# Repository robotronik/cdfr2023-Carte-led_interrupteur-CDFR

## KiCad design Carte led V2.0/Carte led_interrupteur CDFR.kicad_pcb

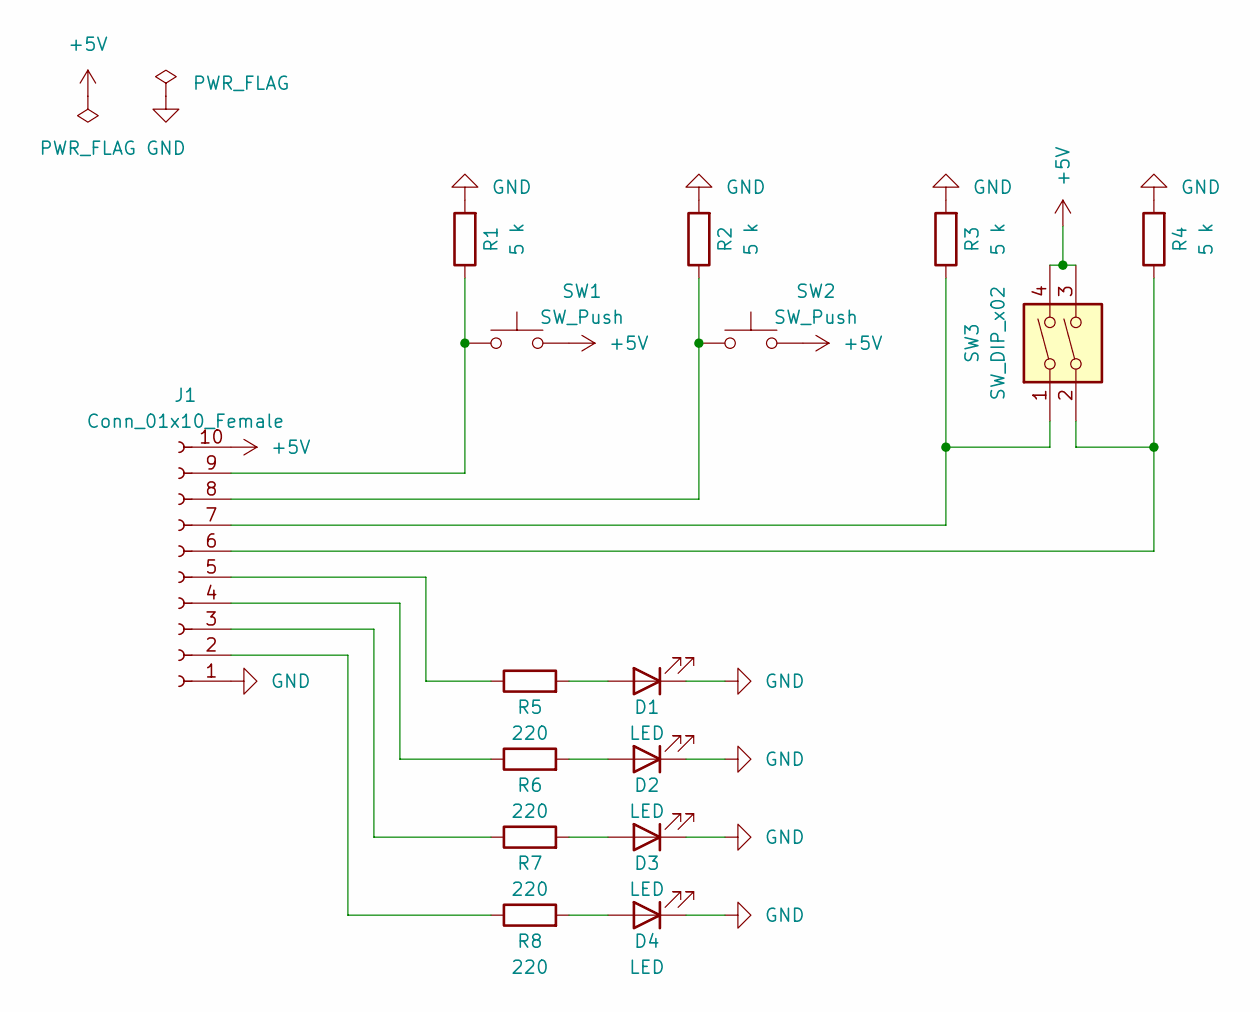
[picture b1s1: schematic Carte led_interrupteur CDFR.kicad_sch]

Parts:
D1, D2, D3, D4: LED; LED_D3.0mm
J1: Conn_01x10_Female; PinHeader_2x05_P2.54mm_Vertical
R1, R2, R3, R4: 5 k; R_Axial_DIN0207_L6.3mm_D2.5mm_P10.16mm_Horizontal
R5, R6, R7, R8: 220; R_Axial_DIN0207_L6.3mm_D2.5mm_P10.16mm_Horizontal
SW1, SW2: SW_Push; SW_PUSH_6mm_H7.3mm
SW3: SW_DIP_x02; SW_DIP_SPSTx02_Slide_9.78x7.26mm_W7.62mm_P2.54mm

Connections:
+5V: J1.10, SW1.2, SW2.2, SW3.3, SW3.4
GND: D1.1 (K), D2.1 (K), D3.1 (K), D4.1 (K), J1.1, R1.2, R2.2, R3.2, R4.2
unnamed: D1.2 (A), R5.2
unnamed: D2.2 (A), R6.2
unnamed: D3.2 (A), R7.2
unnamed: D4.2 (A), R8.2
unnamed: J1.2, R8.1
unnamed: J1.3, R7.1
unnamed: J1.4, R6.1
unnamed: J1.5, R5.1
unnamed: J1.6, R4.1, SW3.2
unnamed: J1.7, R3.1, SW3.1
unnamed: J1.8, R2.1, SW2.1
unnamed: J1.9, R1.1, SW1.1

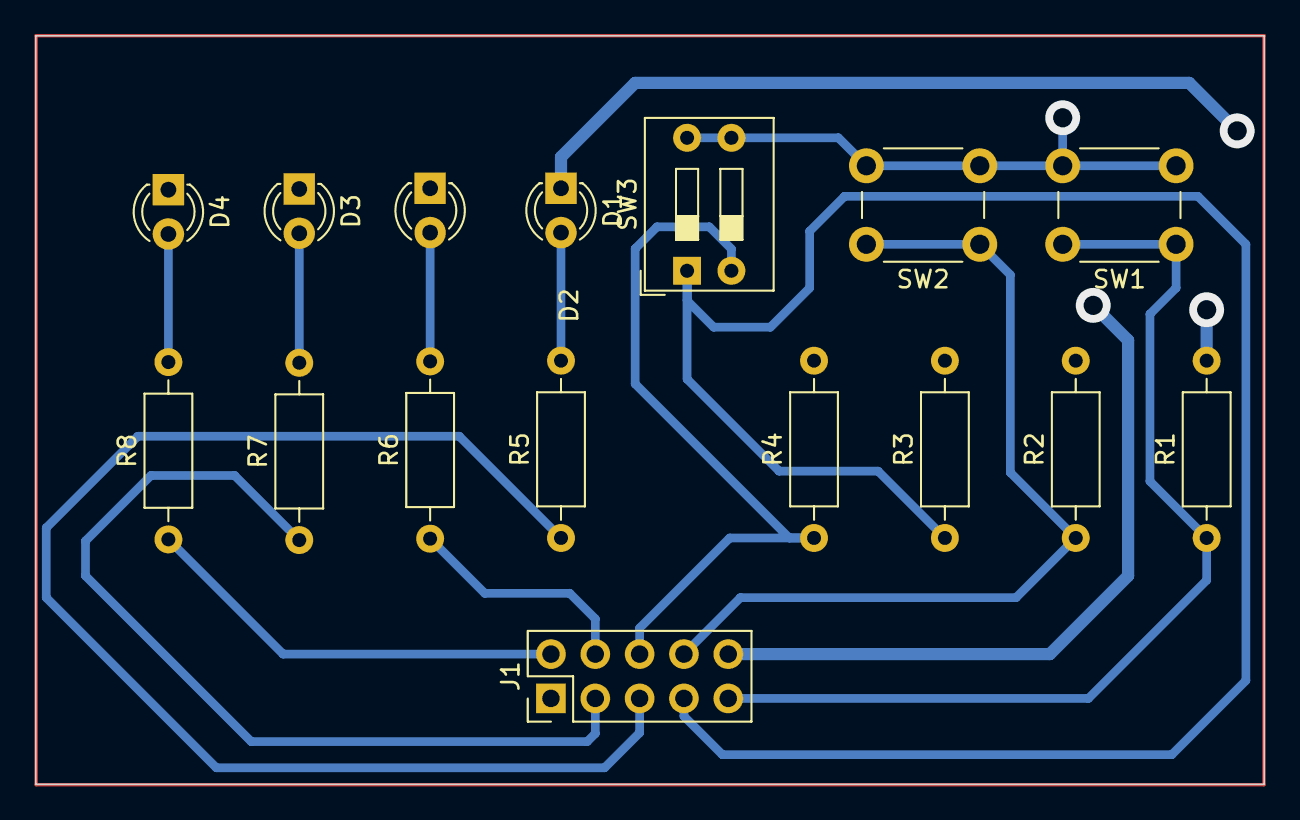
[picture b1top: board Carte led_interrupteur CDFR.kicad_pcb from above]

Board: 2 copper layers, 70.4 x 42.9 mm, 16 parts (0 on the bottom side), 14 nets.

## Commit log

2023-04-09 change pin header
2023-04-18 mise à jour pin header 2x5
